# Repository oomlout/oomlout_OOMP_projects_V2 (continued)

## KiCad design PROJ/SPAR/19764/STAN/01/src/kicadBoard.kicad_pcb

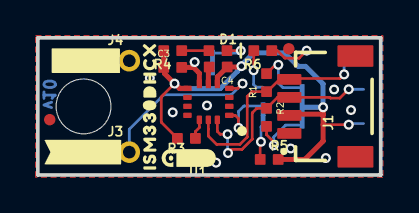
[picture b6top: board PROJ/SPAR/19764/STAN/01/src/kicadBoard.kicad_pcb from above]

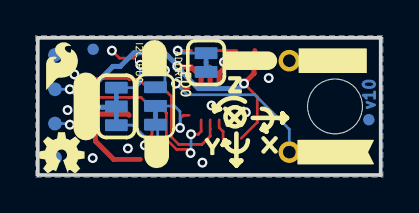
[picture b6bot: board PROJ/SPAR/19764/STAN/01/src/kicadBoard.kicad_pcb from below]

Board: 2 copper layers, 19.1 x 7.6 mm, 42 parts (20 on the bottom side), 13 nets.

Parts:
ADDR0: JUMPER-SMT_3_1-NC_TRACE_SILK; SMT-JUMPER_3_1-NC_TRACE_SILK
C3, C4: 0.1uF; 0402-TIGHT
D1: RED; LED-0402
FD1, FD2: FIDUCIALUFIDUCIAL; FIDUCIAL-MICRO
FID1, FID2: FIDUCIALUFIDUCIAL; FIDUCIAL-MICRO
FRAME1: FRAME-LETTER; CREATIVE_COMMONS
I2C_PU0: S_MODE; SMT-JUMPER_3_2-NC_TRACE_SILK
J1: Qwiic Right Angle; JST04_1MM_RA
J3, J4: 1X01_1MM_NO_SILK
LED0: JUMPER-SMT_2_NC_TRACE_SILK; SMT-JUMPER_2_NC_TRACE_SILK
LOGO1: QWIIC_LOGO_3MM; QWIIC_3MM
LOGO2: OSHW-LOGOMINI; OSHW-LOGO-MINI
LOGO3: SFE_LOGO_NAME_FLAMEBLANK; BLANK
R1, R2: 2.2k; 0402-TIGHT
R3, R5, R6: 10k; 0402-TIGHT
R4: 1k; 0402-TIGHT
STANDOFF1: STAND-OFFTIGHT; STAND-OFF-TIGHT
TP1, TP2, TP3, TP4: TEST-POINT3; PAD.03X.03
U1: ISM330DHCX; LGA-14L
U$1: #0#4
U$2: #1#4
U$3: #LED#2121
U$4, U$10: #GND#4
U$5: #INT1#0
U$6: ISM330DHCX2120
U$7: X2114
U$8: Y2115
U$9: Z2116
U$11: #INT1#2
U$12: #I2C#4
U$29: SFE_LOGO_FLAME_.1

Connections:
3.3V: C3.1, C4.1, I2C_PU0.2, J1.2, R3.2, R4.2, R5.2, TP3.1, U1.P5, U1.P8
GND: C3.2, C4.2, J1.1, J4.1, LED0.1, R6.1, TP4.1, U1.P6, U1.P7
INT1: J3.1, U1.P4
unnamed: ADDR0.3, R5.1
unnamed: D1.A, R4.1
unnamed: D1.C, LED0.2
unnamed: R3.1, U1.P12
unnamed: I2C_PU0.1, R1.2
unnamed: I2C_PU0.3, R2.2
unnamed: ADDR0.1, R6.2
SA0: ADDR0.2, U1.P1
SCL: J1.4, R1.1, TP1.1, U1.P13
SDA: J1.3, R2.1, TP2.1, U1.P14

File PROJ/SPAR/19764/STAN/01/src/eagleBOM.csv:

"Part";"Value";"Device";"Package";"Description";"DESIGNER";"PROD_ID";"REV";"VALUE";
"ADDR";"JUMPER-SMT_3_1-NC_TRACE_SILK";"JUMPER-SMT_3_1-NC_TRACE_SILK";"SMT-JUMPER_3_1-NC_TRACE_SILK";"Normally closed trace jumper (1 of 2 connections)";"";"";"";"";
"C3";"0.1uF";"0.1UF-0402T-6.3V-10%-X7R";"0402-TIGHT";"0.1µF ceramic capacitors";"";"CAP-14993";"";"0.1uF";
"C4";"0.1uF";"0.1UF-0402T-6.3V-10%-X7R";"0402-TIGHT";"0.1µF ceramic capacitors";"";"CAP-14993";"";"0.1uF";
"D1";"RED";"LED-RED_0402";"LED-0402";"Red SMD LED";"";"DIO-16757";"";"RED";
"FD1";"FIDUCIALUFIDUCIAL";"FIDUCIALUFIDUCIAL";"FIDUCIAL-MICRO";"Fiducial Alignment Points";"";"";"";"";
"FD2";"FIDUCIALUFIDUCIAL";"FIDUCIALUFIDUCIAL";"FIDUCIAL-MICRO";"Fiducial Alignment Points";"";"";"";"";
"FID1";"FIDUCIALUFIDUCIAL";"FIDUCIALUFIDUCIAL";"FIDUCIAL-MICRO";"Fiducial Alignment Points";"";"";"";"";
"FID2";"FIDUCIALUFIDUCIAL";"FIDUCIALUFIDUCIAL";"FIDUCIAL-MICRO";"Fiducial Alignment Points";"";"";"";"";
"FRAME1";"FRAME-LETTER";"FRAME-LETTER";"CREATIVE_COMMONS";"Schematic Frame - Letter";"Elias Santistevan";"";"";"";
"I2C_PU";"S_MODE";"JUMPER-SMT_3_2-NC_TRACE_SILK";"SMT-JUMPER_3_2-NC_TRACE_SILK";"Normally closed trace jumper (2 of 2 connections)";"";"";"";"";
"J1";"Qwiic Right Angle";"I2C_STANDARDQWIIC";"JST04_1MM_RA";"SparkFun I2C Standard Pinout Header";"";"CONN-13694";"";"Qwiic Right Angle";
"J3";"";"CONN_01_1MM";"1X01_1MM_NO_SILK";"Single connection point. Often used as Generic Header-pin footprint for 0.1 inch spaced/style header connections";"";"";"";"";
"J4";"";"CONN_01_1MM";"1X01_1MM_NO_SILK";"Single connection point. Often used as Generic Header-pin footprint for 0.1 inch spaced/style header connections";"";"";"";"";
"LED";"JUMPER-SMT_2_NC_TRACE_SILK";"JUMPER-SMT_2_NC_TRACE_SILK";"SMT-JUMPER_2_NC_TRACE_SILK";"Normally closed trace jumper";"";"";"";"";
"LOGO1";"QWIIC_LOGO_3MM";"QWIIC_LOGO_3MM";"QWIIC_3MM";"Qwiic Logos for placement on schematic and PCB. The 5.5mm silk logo is best for placing next to Qwiic connector.";"";"";"";"";
"LOGO2";"OSHW-LOGOMINI";"OSHW-LOGOMINI";"OSHW-LOGO-MINI";"Open-Source Hardware (OSHW) Logo";"";"";"";"";
"LOGO3";"SFE_LOGO_NAME_FLAMEBLANK";"SFE_LOGO_NAME_FLAMEBLANK";"BLANK";"SparkFun Font Logo w/ Flame";"";"";"";"";
"R1";"2.2k";"2.2KOHM-0402T-1/16W-1%";"0402-TIGHT";"2.2kΩ resistor";"";"RES-14341";"";"2.2k";
"R2";"2.2k";"2.2KOHM-0402T-1/16W-1%";"0402-TIGHT";"2.2kΩ resistor";"";"RES-14341";"";"2.2k";
"R3";"10k";"10KOHM-0402T-1/16W-1%";"0402-TIGHT";"10kΩ resistor";"";"RES-14241";"";"10k";
"R4";"1k";"1KOHM-0402T-1/16W-1%";"0402-TIGHT";"1kΩ resistor";"";"RES-14342";"";"1k";
"R5";"10k";"10KOHM-0402T-1/16W-1%";"0402-TIGHT";"10kΩ resistor";"";"RES-14241";"";"10k";
"R6";"10k";"10KOHM-0402T-1/16W-1%";"0402-TIGHT";"10kΩ resistor";"";"RES-14241";"";"10k";
"STANDOFF1";"STAND-OFFTIGHT";"STAND-OFFTIGHT";"STAND-OFF-TIGHT";"Stand Off";"";"";"";"";
"TP1";"TEST-POINT3";"TEST-POINT3";"PAD.03X.03";"SparkFun Test Points";"";"";"";"";
"TP2";"TEST-POINT3";"TEST-POINT3";"PAD.03X.03";"SparkFun Test Points";"";"";"";"";
"TP3";"TEST-POINT3";"TEST-POINT3";"PAD.03X.03";"SparkFun Test Points";"";"";"";"";
"TP4";"TEST-POINT3";"TEST-POINT3";"PAD.03X.03";"SparkFun Test Points";"";"";"";"";
"U1";"ISM330DHCX";"ISM330DHCX";"LGA-14L";"ISM330DHCX 6DoF";"";"IC-16693";"";"";

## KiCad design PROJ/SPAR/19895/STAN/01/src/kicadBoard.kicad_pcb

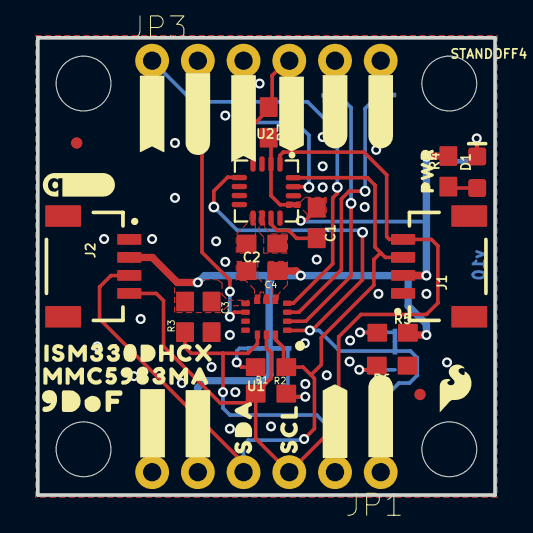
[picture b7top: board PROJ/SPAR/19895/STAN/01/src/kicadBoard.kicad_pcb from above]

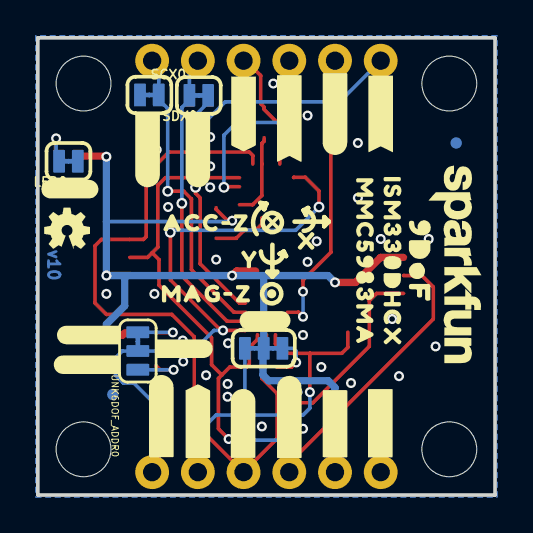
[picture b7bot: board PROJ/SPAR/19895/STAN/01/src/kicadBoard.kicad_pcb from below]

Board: 2 copper layers, 25.4 x 25.4 mm, 76 parts (33 on the bottom side), 19 nets.

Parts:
C1: 1.0uF; 0603
C2: 10uF; 0603
C3, C4: 0.1uF; 0603
D1: RED; LED-0603
FD1, FD2: FIDUCIALUFIDUCIAL; FIDUCIAL-MICRO
FID1, FID2: FIDUCIALUFIDUCIAL; FIDUCIAL-MICRO
FRAME2: FRAME-LEDGER; CREATIVE_COMMONS
I2C_PU0: S_MODE; SMT-JUMPER_3_2-NC_TRACE_SILK
J1, J2: QWIIC_RIGHT_ANGLE; JST04_1MM_RA
JP1, JP3: IO; 1X06_NO_SILK
LED0: JUMPER-SMT_2_NC_TRACE_SILK; SMT-JUMPER_2_NC_TRACE_SILK
LOGO1: QWIIC_LOGO_4MM; QWIIC_4MM
LOGO2: OSHW-LOGOMINI; OSHW-LOGO-MINI
LOGO3: SFE_LOGO_NAME.1_INCH; SFE_LOGO_NAME_.1
R1, R2: 2.2k; 0603
R3, R5, R6, R7: 100k; 0603
R4: 1k; 0603
SCX0: JUMPER-SMT_2_NC_TRACE_SILK; SMT-JUMPER_2_NC_TRACE_SILK
SDX0: JUMPER-SMT_2_NC_TRACE_SILK; SMT-JUMPER_2_NC_TRACE_SILK
STANDOFF1, STANDOFF2, STANDOFF3, STANDOFF4: STAND-OFFTIGHT; STAND-OFF-TIGHT
U1: ISM330DHCX; LGA-14L
U2: MMC5983MA_QFN16; LGA-16-3X3MM-4X4PINS
U$1, U$15: #3V3#1
U$2, U$17: #GND#0
U$3, U$7: ISM330DHCX331
U$4: SDA14
U$5: SCL13
U$6: #POCI#11
U$8: #INT1#0
U$9: #INT2#3
U$10: #INT1#2
U$11: #INT2#2
U$12: #MINT#4
U$13: ACC#Z5985
U$14: MAG#Z5984
U$16: #LED#11
U$18: #POCI#12
U$19: ##MCS##5
U$20: #SDX#7
U$21, U$32: MMC5983MA24
U$22: #SCL#5
U$23: #SCX#8
U$24, U$30: 9DOF24
U$25: #I2C#11
U$26: #PICO#13
U$27: ##ACS##6
U$28: PWR8
U$29: SFE_LOGO_FLAME_.1
U$31: #MINT#5
U$33: #0X6A#15
U$34: ##MCS##7
U$35: #SDX#9
U$36: #SCX#11
U$37: X2114
U$38: Y2115
U$39: ##ACS##8
U$40: #0X6B#15
U$41: #ACC#17
UNK6DOF_ADDR0: JUMPER-SMT_3_1-NC_TRACE_SILK; SMT-JUMPER_3_1-NC_TRACE_SILK

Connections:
3.3V: C1.1, C3.1, C4.1, I2C_PU0.2, J1.2, J2.2, JP1.5, R3.2, R4.2, R5.2, R7.2, U1.P5, U1.P8, U2.2, U2.13
CAP: C2.1, U2.10
GND: C1.2, C2.2, C3.2, C4.2, J1.1, J2.1, JP1.6, LED0.1, R6.1, SCX0.1, SDX0.1, U1.P6, U1.P7, U2.9, U2.11
ISM_INT1: JP3.1, U1.P4
ISM_INT2: JP3.2, U1.P9
MAG_INT: JP3.3, U2.15
unnamed: R5.1, UNK6DOF_ADDR0.3
unnamed: D1.A, R4.1
unnamed: D1.C, LED0.2
unnamed: I2C_PU0.1, R1.2
unnamed: I2C_PU0.3, R2.2
unnamed: R6.2, UNK6DOF_ADDR0.1
POCI/SA0: JP1.1, U1.P1, U2.5, UNK6DOF_ADDR0.2
SCL/SCK: J1.4, J2.4, JP1.3, R1.1, U1.P13, U2.1
SCX: JP3.6, SCX0.2, U1.P3
SDA/PICO: J1.3, J2.3, JP1.4, R2.1, U1.P14, U2.16
SDX: JP3.5, SDX0.2, U1.P2
~ISM_CS: JP1.2, R3.1, U1.P12
~MAG_CS: JP3.4, R7.1, U2.4

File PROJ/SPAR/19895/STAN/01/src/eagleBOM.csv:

"Part";"Value";"Device";"Package";"Description";"DESIGNER";"PROD_ID";"REV";"VALUE";
"6DOF_ADDR";"JUMPER-SMT_3_1-NC_TRACE_SILK";"JUMPER-SMT_3_1-NC_TRACE_SILK";"SMT-JUMPER_3_1-NC_TRACE_SILK";"Normally closed trace jumper (1 of 2 connections)";"";"";"";"";
"C1";"1.0uF";"1.0UF-0603-16V-10%";"0603";"1µF ceramic capacitors";"";"CAP-00868";"";"1.0uF";
"C2";"10uF";"10UF-0603-6.3V-20%";"0603";"10.0µF ceramic capacitors";"";"CAP-11015";"";"10uF";
"C3";"0.1uF";"0.1UF-0603-25V-(+80/-20%)";"0603";"0.1µF ceramic capacitors";"";"CAP-00810";"";"0.1uF";
"C4";"0.1uF";"0.1UF-0603-25V-(+80/-20%)";"0603";"0.1µF ceramic capacitors";"";"CAP-00810";"";"0.1uF";
"D1";"RED";"LED-RED0603";"LED-0603";"Red SMD LED";"";"DIO-00819";"";"RED";
"FD1";"FIDUCIALUFIDUCIAL";"FIDUCIALUFIDUCIAL";"FIDUCIAL-MICRO";"Fiducial Alignment Points";"";"";"";"";
"FD2";"FIDUCIALUFIDUCIAL";"FIDUCIALUFIDUCIAL";"FIDUCIAL-MICRO";"Fiducial Alignment Points";"";"";"";"";
"FID1";"FIDUCIALUFIDUCIAL";"FIDUCIALUFIDUCIAL";"FIDUCIAL-MICRO";"Fiducial Alignment Points";"";"";"";"";
"FID2";"FIDUCIALUFIDUCIAL";"FIDUCIALUFIDUCIAL";"FIDUCIAL-MICRO";"Fiducial Alignment Points";"";"";"";"";
"FRAME2";"FRAME-LEDGER";"FRAME-LEDGER";"CREATIVE_COMMONS";"Schematic Frame - Ledger";"";"";"";"";
"I2C_PU";"S_MODE";"JUMPER-SMT_3_2-NC_TRACE_SILK";"SMT-JUMPER_3_2-NC_TRACE_SILK";"Normally closed trace jumper (2 of 2 connections)";"";"";"";"";
"J1";"QWIIC_RIGHT_ANGLE";"QWIIC_CONNECTORJS-1MM";"JST04_1MM_RA";"SparkFun I2C Standard Qwiic Connector";"";"CONN-13694";"";"QWIIC_RIGHT_ANGLE";
"J2";"QWIIC_RIGHT_ANGLE";"QWIIC_CONNECTORJS-1MM";"JST04_1MM_RA";"SparkFun I2C Standard Qwiic Connector";"";"CONN-13694";"";"QWIIC_RIGHT_ANGLE";
"JP1";"IO";"CONN_06NO_SILK_NO_POP";"1X06_NO_SILK";"Multi connection point. Often used as Generic Header-pin footprint for 0.1 inch spaced/style header connections";"";"";"";"";
"JP3";"IO";"CONN_06NO_SILK_NO_POP";"1X06_NO_SILK";"Multi connection point. Often used as Generic Header-pin footprint for 0.1 inch spaced/style header connections";"";"";"";"";
"LED";"JUMPER-SMT_2_NC_TRACE_SILK";"JUMPER-SMT_2_NC_TRACE_SILK";"SMT-JUMPER_2_NC_TRACE_SILK";"Normally closed trace jumper";"";"";"";"";
"LOGO1";"QWIIC_LOGO_4MM";"QWIIC_LOGO_4MM";"QWIIC_4MM";"Qwiic Logos for placement on schematic and PCB. The 5.5mm silk logo is best for placing next to Qwiic connector.";"";"";"";"";
"LOGO2";"OSHW-LOGOMINI";"OSHW-LOGOMINI";"OSHW-LOGO-MINI";"Open-Source Hardware (OSHW) Logo";"";"";"";"";
"LOGO3";"SFE_LOGO_NAME.1_INCH";"SFE_LOGO_NAME.1_INCH";"SFE_LOGO_NAME_.1";"SparkFun Font Logo";"";"";"";"";
"R1";"2.2k";"2.2KOHM-0603-1/10W-1%";"0603";"2.2kΩ resistor";"";"RES-08272";"";"2.2k";
"R2";"2.2k";"2.2KOHM-0603-1/10W-1%";"0603";"2.2kΩ resistor";"";"RES-08272";"";"2.2k";
"R3";"100k";"100KOHM-0603-1/10W-1%";"0603";"100kΩ resistor";"";"RES-07828";"";"100k";
"R4";"1k";"1KOHM-0603-1/10W-1%";"0603";"1kΩ resistor";"";"RES-07856";"";"1k";
"R5";"100k";"100KOHM-0603-1/10W-1%";"0603";"100kΩ resistor";"";"RES-07828";"";"100k";
"R6";"100k";"100KOHM-0603-1/10W-1%";"0603";"100kΩ resistor";"";"RES-07828";"";"100k";
"R7";"100k";"100KOHM-0603-1/10W-1%";"0603";"100kΩ resistor";"";"RES-07828";"";"100k";
"SCX";"JUMPER-SMT_2_NC_TRACE_SILK";"JUMPER-SMT_2_NC_TRACE_SILK";"SMT-JUMPER_2_NC_TRACE_SILK";"Normally closed trace jumper";"";"";"";"";
"SDX";"JUMPER-SMT_2_NC_TRACE_SILK";"JUMPER-SMT_2_NC_TRACE_SILK";"SMT-JUMPER_2_NC_TRACE_SILK";"Normally closed trace jumper";"";"";"";"";
"STANDOFF1";"STAND-OFFTIGHT";"STAND-OFFTIGHT";"STAND-OFF-TIGHT";"Stand Off";"";"";"";"";
"STANDOFF2";"STAND-OFFTIGHT";"STAND-OFFTIGHT";"STAND-OFF-TIGHT";"Stand Off";"";"";"";"";
"STANDOFF3";"STAND-OFFTIGHT";"STAND-OFFTIGHT";"STAND-OFF-TIGHT";"Stand Off";"";"";"";"";
"STANDOFF4";"STAND-OFFTIGHT";"STAND-OFFTIGHT";"STAND-OFF-TIGHT";"Stand Off";"";"";"";"";
"U1";"ISM330DHCX";"ISM330DHCX";"LGA-14L";"ISM330DHCX 6DoF";"";"IC-16693";"";"";
"U2";"MMC5983MA_QFN16";"MMC5983MA_QFN16";"LGA-16-3X3MM-4X4PINS";"High Performance 3-axis Magnetic Sensor";"";"IC-16314";"";"";

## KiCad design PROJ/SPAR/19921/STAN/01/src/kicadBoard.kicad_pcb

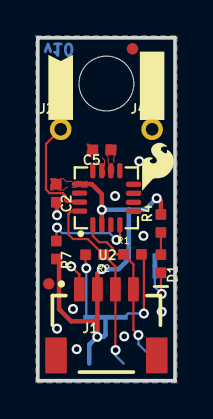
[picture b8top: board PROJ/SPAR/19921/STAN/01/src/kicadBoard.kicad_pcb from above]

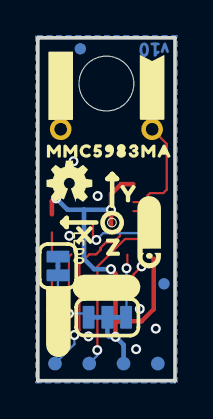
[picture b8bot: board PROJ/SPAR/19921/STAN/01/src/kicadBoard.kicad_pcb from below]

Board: 2 copper layers, 7.6 x 19.0 mm, 37 parts (18 on the bottom side), 11 nets.

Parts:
C2: 1.0uF; 0402-TIGHT
C5: 10uF; 0402-TIGHT
D1: RED; LED-0402
FD1, FD2: FIDUCIALUFIDUCIAL; FIDUCIAL-MICRO
FID1, FID2: FIDUCIALUFIDUCIAL; FIDUCIAL-MICRO
FRAME1: FRAME-LETTER; CREATIVE_COMMONS
I2C_PU0: S_MODE; SMT-JUMPER_3_2-NC_TRACE_SILK
J1: QWIIC_RIGHT_ANGLE; JST04_1MM_RA
J2, J4: 1X01_1MM_NO_SILK
LED0: JUMPER-SMT_2_NC_TRACE_SILK; SMT-JUMPER_2_NC_TRACE_SILK
LOGO1: QWIIC_LOGO_4MM; QWIIC_4MM
LOGO2: OSHW-LOGOMINI; OSHW-LOGO-MINI
LOGO3: SFE_LOGO_NAMEBLANK; BLANK
R1, R2: 2.2k; 0402-TIGHT
R4: 1k; 0402-TIGHT
R7: 100k; 0402-TIGHT
STANDOFF3: STAND-OFFTIGHT; STAND-OFF-TIGHT
TP1, TP2, TP3, TP5: TEST-POINT3; PAD.03X.03
U2: MMC5983MA_QFN16; LGA-16-3X3MM-4X4PINS
U$1: #INT#20
U$2: MMC5983MA331
U$3: #I2C#4
U$4, U$6: #GND#4
U$5: #INT#21
U$8: X2114
U$9: Y2115
U$10: Z2116
U$11: #LED#5
U$29: SFE_LOGO_FLAME_.1

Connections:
3.3V: C2.1, I2C_PU0.2, J1.2, R4.2, R7.2, TP1.1, U2.2, U2.13
CAP: C5.1, U2.10
GND: C2.2, C5.2, J1.1, J4.1, LED0.1, TP5.1, U2.9, U2.11
INT: J2.1, U2.15
unnamed: D1.A, R4.1
unnamed: D1.C, LED0.2
unnamed: I2C_PU0.1, R1.2
unnamed: I2C_PU0.3, R2.2
SCL: J1.4, R1.1, TP3.1, U2.1
SDA: J1.3, R2.1, TP2.1, U2.16
~MAG_CS: R7.1, U2.4
